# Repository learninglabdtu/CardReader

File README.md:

CardReader
==========

RFID Card Reader lock for closets.

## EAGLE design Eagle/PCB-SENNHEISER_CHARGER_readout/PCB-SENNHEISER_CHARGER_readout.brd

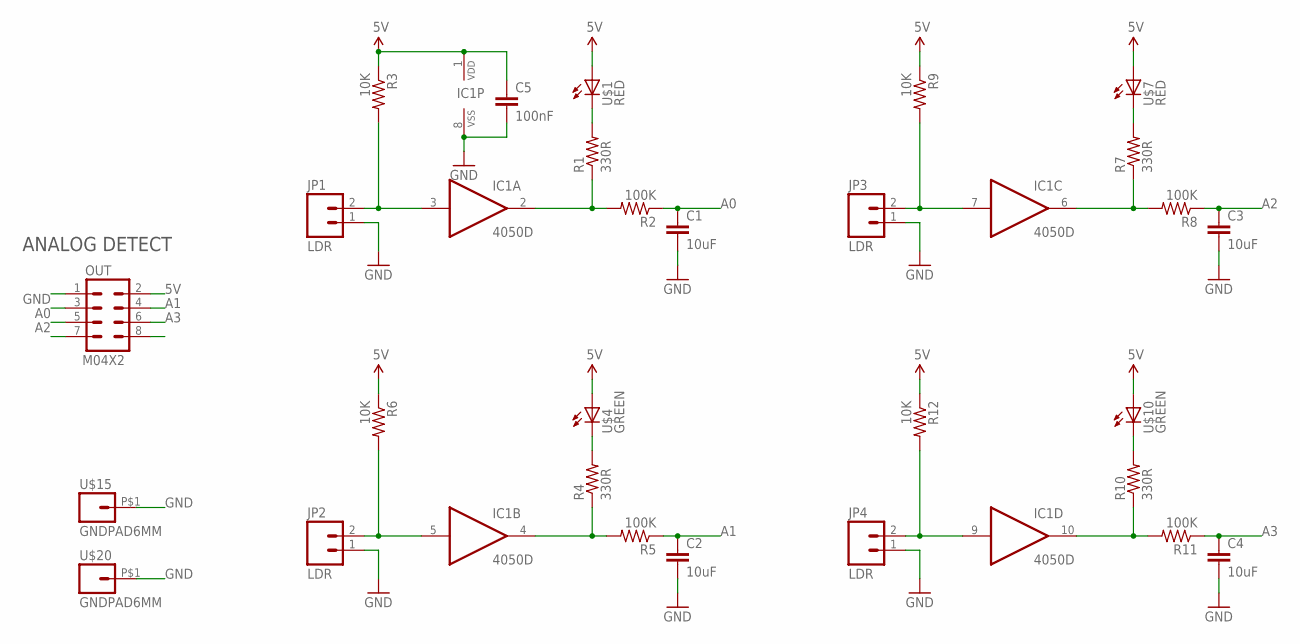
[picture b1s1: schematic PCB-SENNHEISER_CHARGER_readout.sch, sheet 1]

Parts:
C1, C2, C3, C4: 10uF; 0603-CAP
C5: 100nF; 0603-CAP
IC1: 4050D; SO16
JP1, JP2, JP3, JP4: LDR; 1X02
OUT: M04X2; 2X4
R1, R4, R7, R10: 330R; 0603-RES
R2, R5, R8, R11: 100K; 0603-RES
R3, R6, R9, R12: 10K; 0603-RES
U$1, U$7: RED; LED3MM
U$4, U$10: GREEN; LED3MM
U$15, U$20: GNDPAD6MM; 3.2MMPAD6MM

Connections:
5V: C5.1, IC1.1 (VDD), OUT.2, R3.1, R6.1, R9.1, R12.1, U$1.A, U$4.A, U$7.A, U$10.A
A0: C1.1, OUT.3, R2.1
A1: C2.1, OUT.4, R5.1
A2: C3.1, OUT.5, R8.1
A3: C4.1, OUT.6, R11.1
GND: C1.2, C2.2, C3.2, C4.2, C5.2, IC1.8 (VSS), JP1.1, JP2.1, JP3.1, JP4.1, OUT.1, U$15.P$1, U$20.P$1
unnamed: IC1.3 (I), JP1.2, R3.2
unnamed: R1.2, U$1.K (C)
unnamed: IC1.2 (O), R1.1, R2.2
unnamed: IC1.5 (I), JP2.2, R6.2
unnamed: R4.2, U$4.K (C)
unnamed: IC1.4 (O), R4.1, R5.2
unnamed: IC1.7 (I), JP3.2, R9.2
unnamed: R7.2, U$7.K (C)
unnamed: IC1.6 (O), R7.1, R8.2
unnamed: IC1.9 (I), JP4.2, R12.2
unnamed: R10.2, U$10.K (C)
unnamed: IC1.10 (O), R10.1, R11.2

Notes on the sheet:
ANALOG DETECT

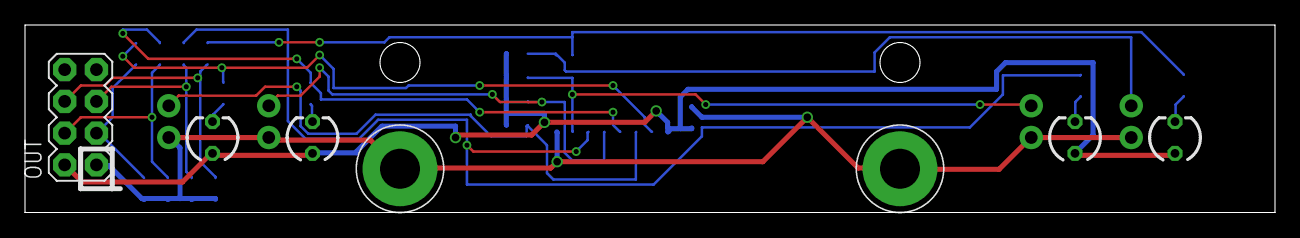
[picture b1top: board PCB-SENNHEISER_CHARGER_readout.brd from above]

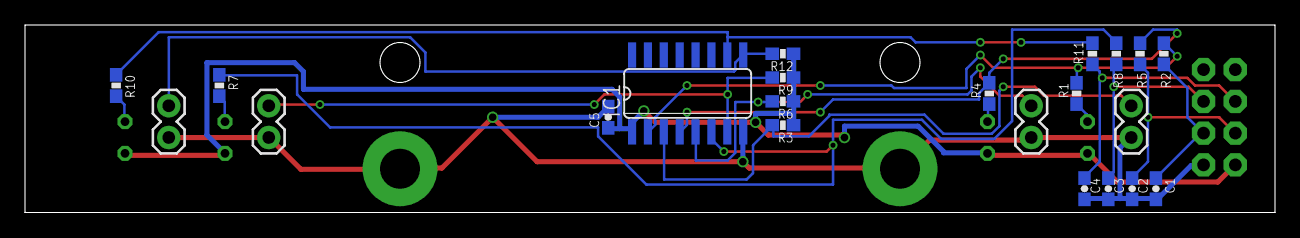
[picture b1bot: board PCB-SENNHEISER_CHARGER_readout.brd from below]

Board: 2 copper layers, 100.0 x 15.0 mm, 29 parts (22 on the bottom side), 18 nets.

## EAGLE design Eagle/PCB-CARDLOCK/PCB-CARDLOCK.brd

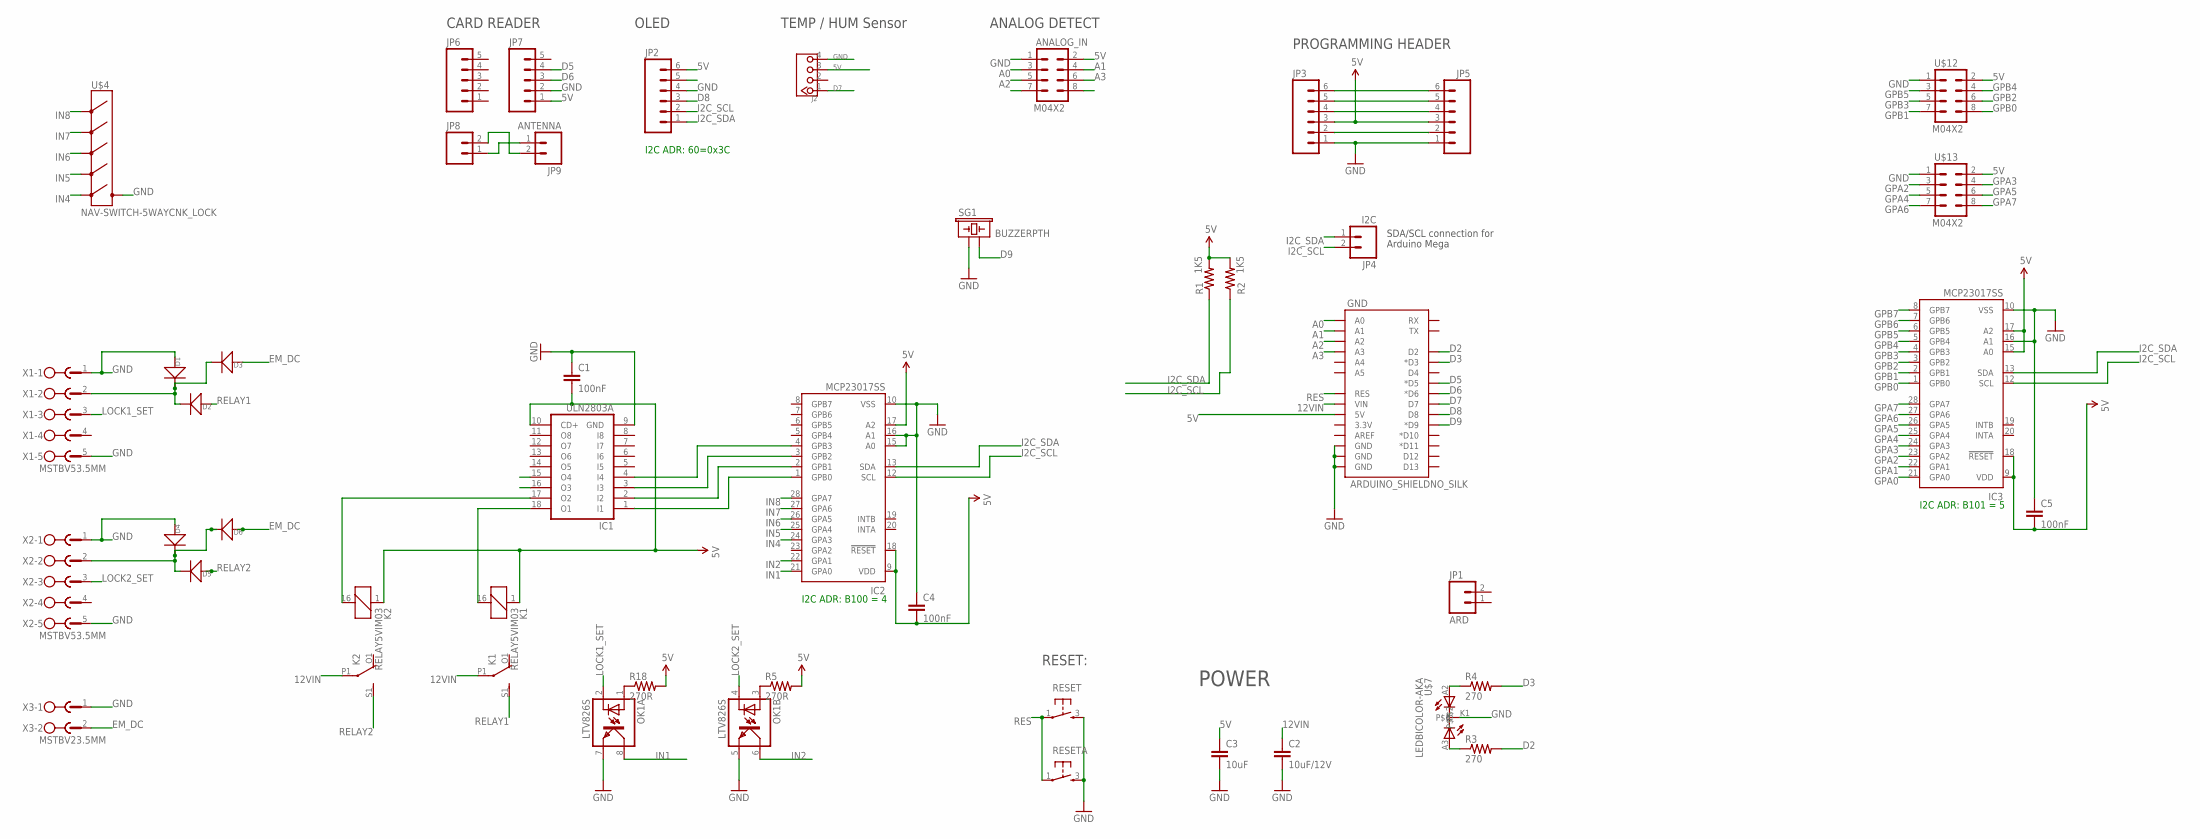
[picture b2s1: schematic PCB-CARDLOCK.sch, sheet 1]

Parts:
ANALOG_IN: M04X2; 2X4
C1: 100nF; 0805
C2: 10uF/12V; 0805
C3: 10uF; 0805
C4, C5: 100nF; 0603-CAP
D1, D2, D3, D4, D5, D6: D-SMA; DO-214AC
GND: ARDUINO_SHIELDNO_SILK; DUEMILANOVE_VIAS
IC1: ULN2803A; SO18W
IC2, IC3: MCP23017SS; SSOP28
J2: TWIG-4P-2.0-2.0; 4P-2.0
JP1: ARD; 1X02
JP2, JP3, JP5: M06POLAR; MOLEX-1X6
JP4: I2C; 1X02
JP6, JP7: M05PTH; 1X05
JP8: M02PTH; 1X02
JP9: ANTENNA; 1X02
K1, K2: RELAY5VIM03; DS2Y
OK1: LTV826S; DIL8-SMD
R1, R2: 1K5; 0603-RES
R3, R4: 270; 0603-RES
R5, R18: 270R; 0603-RES
RESET: TAC_SWITCH; PUSHBUTTON
RESETA: TAC_SWITCH; PUSHBUTTON
SG1: BUZZERPTH; BUZZER-12MM
U$4: NAV-SWITCH-5WAYCNK_LOCK; NAV-SWITCH-5WAY
U$7: LEDBICOLOR-AKA; LED5MM-BICOLOR
U$12, U$13: M04X2; 2X4
X1, X2: MSTBV53.5MM; MSTBV5-3.5
X3: MSTBV23.5MM; MSTBV2-3.5

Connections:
5V: ANALOG_IN.2, C1.2, C3.1, C4.2, C5.2, GND.5V, IC1.10 (CD+), IC2.9 (VDD), IC2.17 (A2), IC2.18 (!RESET), IC3.9 (VDD), IC3.15 (A0), IC3.17 (A2), IC3.18 (!RESET), J2.3, JP2.6, JP3.3, JP5.3, JP7.1, K1.1, K2.1, R1.2, R2.2, R5.2, R18.2, U$12.2, U$13.2
12VIN: C2.1, GND.VIN, K1.P1, K2.P1
A0: ANALOG_IN.3, GND.A0
A1: ANALOG_IN.4, GND.A1
A2: ANALOG_IN.5, GND.A2
A3: ANALOG_IN.6, GND.A3
D2: GND.D2, R3.2
D3: GND.D3 (*D3), R4.2
D5: GND.D5 (*D5), JP7.4
D6: GND.D6 (*D6), JP7.3
D7: GND.D7, J2.1
D8: GND.D8, JP2.3
D9: GND.D9 (*D9), SG1.- (2)
EM_DC: D3.1 (+), D6.1 (+), X3.2
GND: ANALOG_IN.1, C1.1, C2.2, C3.2, C4.1, C5.1, D1.1 (+), D4.1 (+), GND.GND@0 (GND), GND.GND@1 (GND), GND.GND@2 (GND), IC1.9 (GND), IC2.10 (VSS), IC2.15 (A0), IC2.16 (A1), IC3.10 (VSS), IC3.16 (A1), J2.4, JP2.4, JP3.1, JP5.1, JP7.2, OK1.5 (EMIT), OK1.7 (EMIT), RESET.3, RESETA.3, SG1.+ (1), U$4.PIN4 (COMMON), U$7.K1, U$12.1, U$13.1, X1.1, X1.5, X2.1, X2.5, X3.1
GPA0: IC3.21 (GPA0)
GPA1: IC3.22 (GPA1)
GPA2: IC3.23 (GPA2), U$13.3
GPA3: IC3.24 (GPA3), U$13.4
GPA4: IC3.25 (GPA4), U$13.5
GPA5: IC3.26 (GPA5), U$13.6
GPA6: IC3.27 (GPA6), U$13.7
GPA7: IC3.28 (GPA7), U$13.8
GPB0: IC3.1 (GPB0), U$12.8
GPB1: IC3.2 (GPB1), U$12.7
GPB2: IC3.3 (GPB2), U$12.6
GPB3: IC3.4 (GPB3), U$12.5
GPB4: IC3.5 (GPB4), U$12.4
GPB5: IC3.6 (GPB5), U$12.3
GPB6: IC3.7 (GPB6)
GPB7: IC3.8 (GPB7)
I2C_SCL: IC2.12 (SCL), IC3.12 (SCL), JP2.2, JP4.2, R2.1
I2C_SDA: IC2.13 (SDA), IC3.13 (SDA), JP2.1, JP4.1, R1.1
IN1: IC2.21 (GPA0), OK1.8 (COL)
IN2: IC2.22 (GPA1), OK1.6 (COL)
IN4: IC2.24 (GPA3), U$4.PIN6 (PUSH)
IN5: IC2.25 (GPA4), U$4.PIN5 (RIGHT)
IN6: IC2.26 (GPA5), U$4.PIN2 (LEFT)
IN7: IC2.27 (GPA6), U$4.PIN3 (DWN)
IN8: IC2.28 (GPA7), U$4.PIN1 (UP)
LOCK1_SET: OK1.2 (C), X1.3
LOCK2_SET: OK1.4 (C), X2.3
unnamed: D1.2 (-), D2.2 (-), D3.2 (-), X1.2
unnamed: JP8.1, JP9.1
unnamed: JP3.4, JP5.4
unnamed: IC1.18 (O1), K1.16 (2)
unnamed: D4.2 (-), D5.2 (-), D6.2 (-), X2.2
unnamed: IC1.1 (I1), IC2.1 (GPB0)
unnamed: R4.1, U$7.A2
unnamed: JP3.5, JP5.5
unnamed: IC1.17 (O2), K2.16 (2)
unnamed: JP8.2, JP9.2
unnamed: R3.1, U$7.A3
unnamed: JP3.2, JP5.2
unnamed: IC1.2 (I2), IC2.2 (GPB1)
unnamed: IC1.3 (I3), IC2.3 (GPB2)
unnamed: IC1.4 (I4), IC2.4 (GPB3)
unnamed: OK1.3 (A), R5.1
unnamed: OK1.1 (A), R18.1
unnamed: JP3.6, JP5.6
RELAY1: D2.1 (+), K1.S1 (S)
RELAY2: D5.1 (+), K2.S1 (S)
RES: GND.RES, RESET.1, RESETA.1

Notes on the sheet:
SDA/SCL connection for
Arduino Mega
POWER
RESET:
PROGRAMMING HEADER
OLED
CARD READER
TEMP / HUM Sensor
ANALOG DETECT
I2C ADR: B100 = 4
I2C ADR: 60=0x3C
I2C ADR: B101 = 5

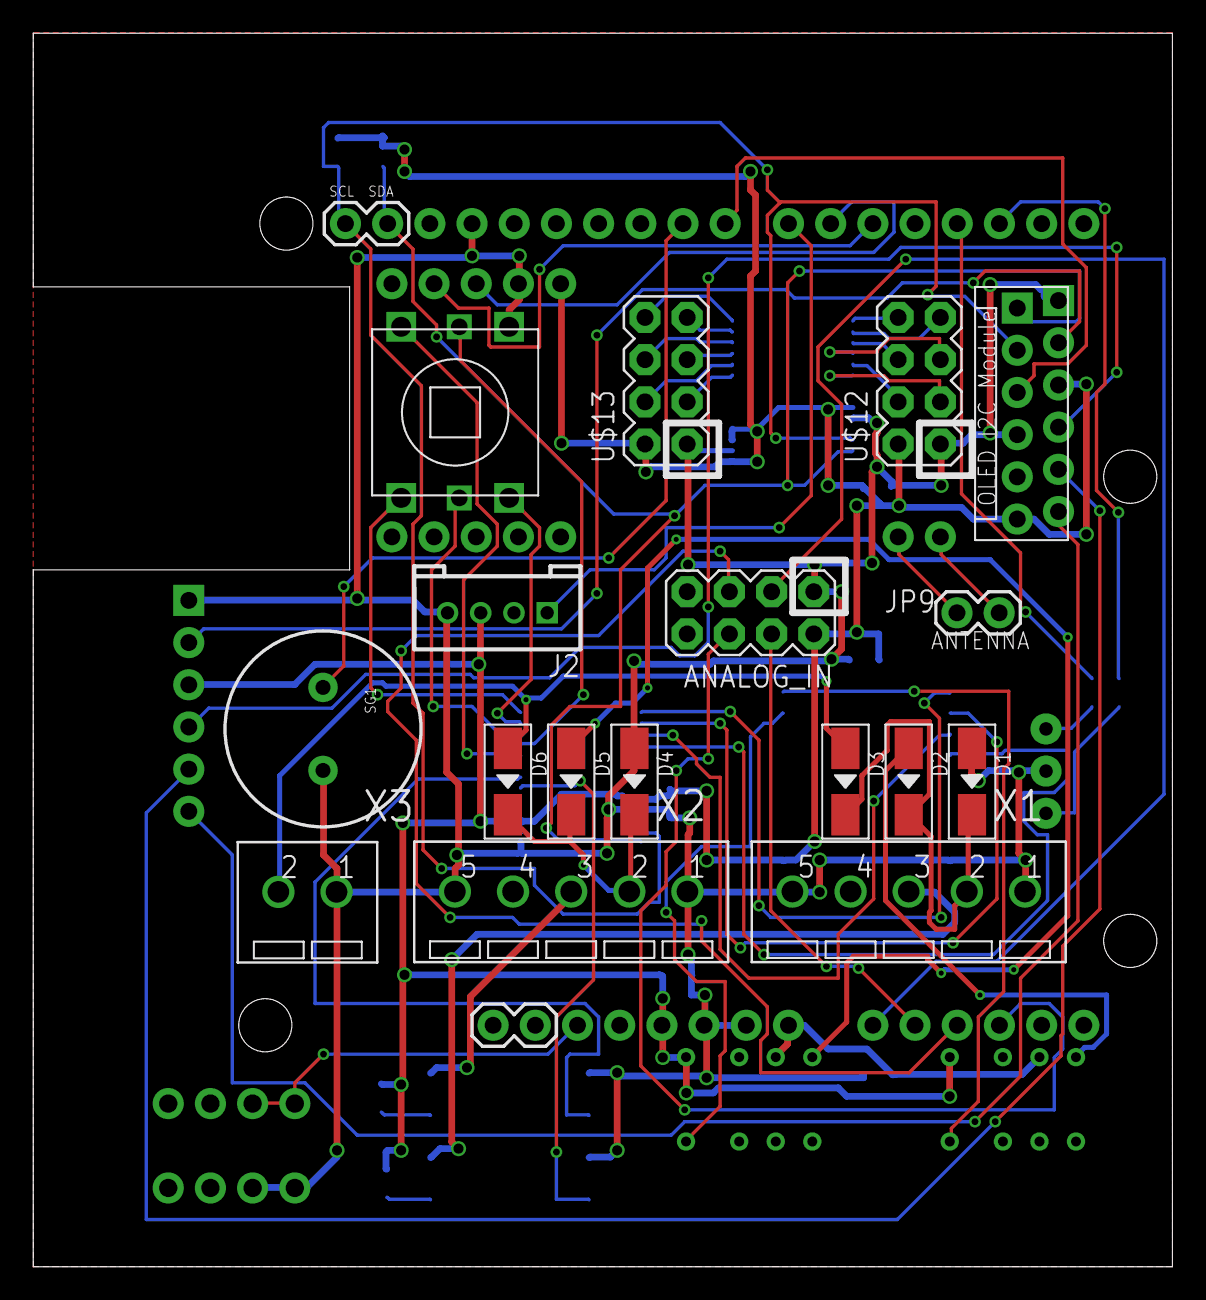
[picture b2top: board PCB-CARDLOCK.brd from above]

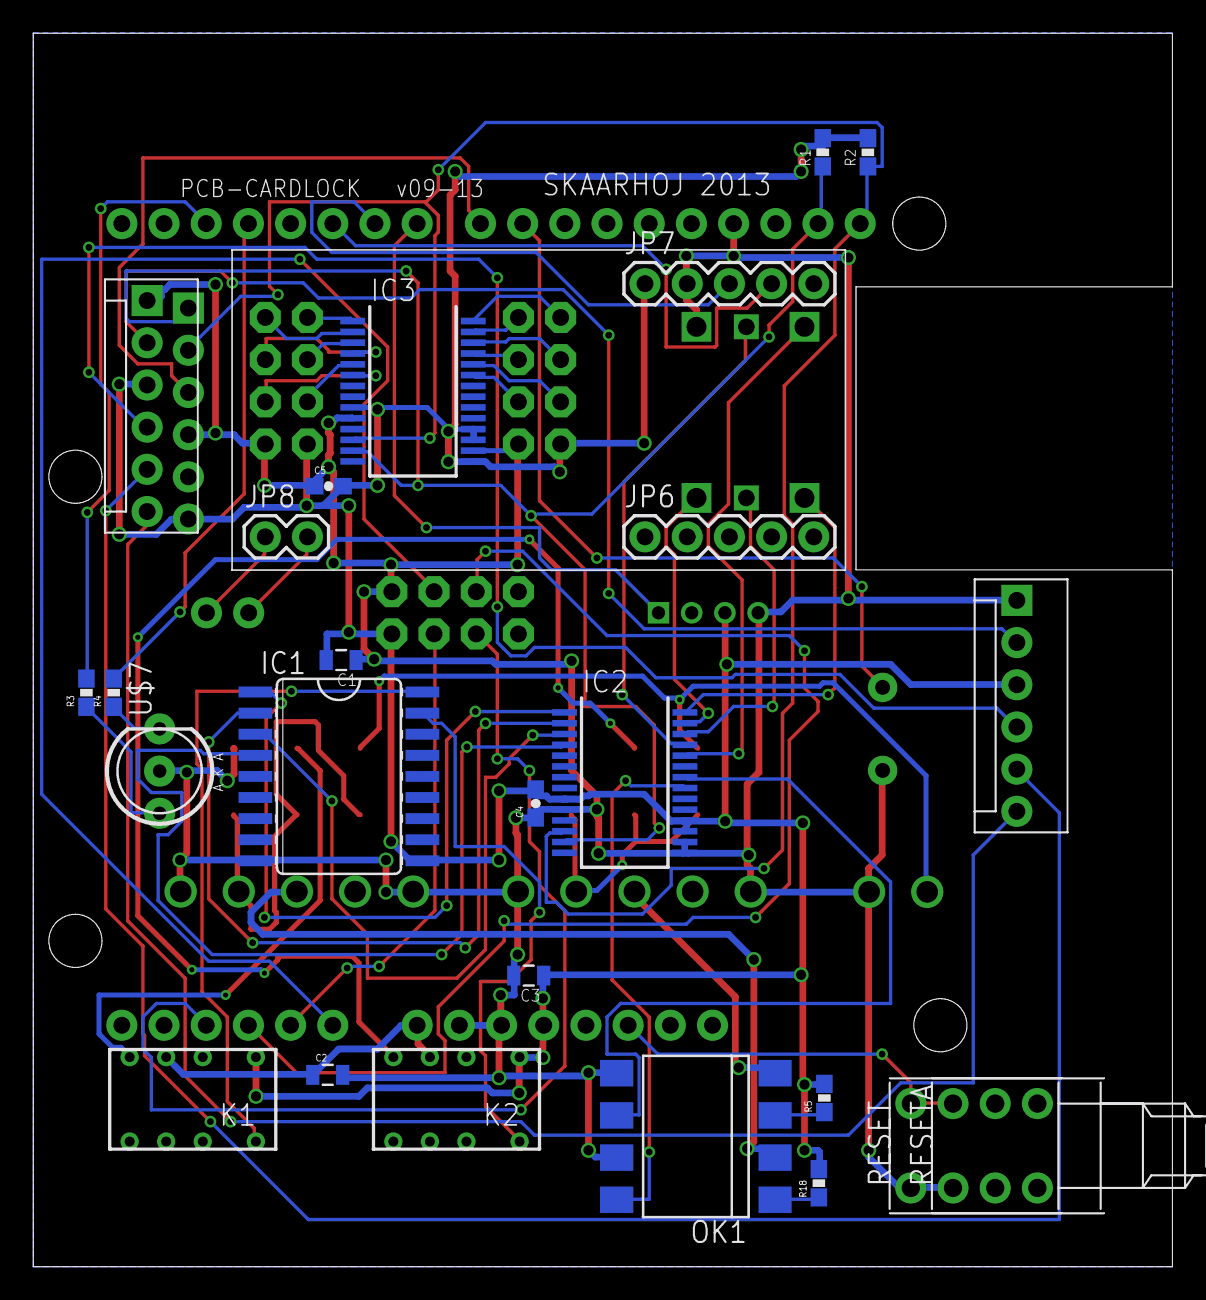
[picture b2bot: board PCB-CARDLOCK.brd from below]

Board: 2 copper layers, 68.6 x 74.3 mm, 45 parts (25 on the bottom side), 59 nets.

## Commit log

2014-01-15 asdf
2014-01-15 Added main bulk of files.

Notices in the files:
parts and their libraries:
SparkFun: Licensing: CC v3.0 Share-Alike You are welcome to use this library for commercial purposes.
